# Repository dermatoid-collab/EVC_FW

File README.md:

# EVC_FW

Progetto hardware e firmware del sistema di controllo di un ascensore domestico a trazione (TTF) di LiftingItalia s.r.l. Quattro schede basate su STM32F446, collegate in CAN; il motore è comandato da un VFD.

## Struttura

| Cartella | Contenuto |
|---|---|
| `TTF-Base/` | Scheda master (STM32F446VC, PCB a 4 strati): schemi e PCB KiCad, Gerber/PDF in `fabs/`, firmware in `Firmware/TTF-Base/`. |
| `TTF-CX/` | Scheda di tetto cabina (STM32F446RC, PCB a 4 strati): ingressi di sicurezza S3/S4, bypass trap/tray, zone di sblocco, cella di carico, illuminazione. Firmware in `Firmware/TTF-CX/`. |
| `UDEC.CX/` | Scheda collegata alla cabina (STM32F446VC, PCB a 4 strati): audio, pulsantiera, interfaccia VFD, cella di carico. Firmware in `CubeMX/`, simulazioni in `LTSpice/`. |
| `Schema Macchina/` | Schema elettrico generale dell'impianto (cabina, cappello, servizi); PDF in `fabs/TTF.pdf`. |
| `F510.05.9019 Scheda Consenso Paracadute/` | PCB a 1 strato della scheda di consenso paracadute e modelli FreeCAD del sensore. |

## Firmware TTF-Base

Super-loop con timer software e macchina a stati, in C (STM32CubeIDE/HAL). Moduli principali in `TTF-Base/Firmware/TTF-Base/Core/`:

- `run_mode.c`: macchina a stati del movimento (`NORMAL`, `UP`, `DOWN`, `OPEN_DOOR`, `CLOSE_DOOR`, `STUCK_UP`, `FALL_TEST`, `WAIT_FOR_CALL_RELEASE`) e sequenza di abilitazione.
- `door.c`: ciclo porte (apertura, chiusura, blocco, sblocco).
- `pmode.c`, `battery.c`, `npb.c`, `ltc2959.c`: commutazione caricabatteria/VFD, gestione e misura della batteria.
- `vfd.c`: comando dell'azionamento (CANopen).
- `trips.c`, `trip_list.h`: gestione degli errori (inattivo, attivo, memorizzato).
- `udec_c.c`, `udec_cx.c`, `l2d.c`, `can.c`: comunicazione CAN con le altre schede.
- `HMI.c`, `HMI_menu.c`, `lcd_hd44780_i2c.c`: display LCD e menu.

Le modifiche recenti sono descritte in `TTF-Base/Firmware/TTF-Base/Changelog`.

## Documentazione

- **`docs/registro_issue.md`: documento base del lavoro.** Tutte le osservazioni, le proposte di correzione, le verifiche e il loro stato. Si aggiorna a ogni issue risolta; il controllo di coerenza è `python3 docs/check_registro.py`.
- `docs/analisi.md`: analisi di partenza (panoramica, revisione del codice di sicurezza, catena delle sicurezze, confronto con i manuali).
- I diagrammi stanno in `docs/diagrammi/`, numerati 01-07; gli script che li generano restano in `docs/`.
- `docs/diagrammi/02.diagramma_funzionale.svg` (e `.png`): diagramma funzionale della macchina (stati del movimento, ciclo porta, alimentazione, batteria, sicurezze, comunicazioni), con i riquadri rossi che rimandano agli ID del registro. Si rigenera con `python3 docs/gen_diagramma_funzionale.py docs/diagrammi/02.diagramma_funzionale.svg`.
- `docs/diagrammi/03.diagramma_funzionale_light.svg` (e `.png`): versione del diagramma funzionale per il dipartimento commerciale (blocchi, una corsa passo per passo, stati, sicurezze, dati di prodotto). Si rigenera con `python3 docs/gen_diagramma_light.py docs/diagrammi/03.diagramma_funzionale_light.svg`.
- `docs/diagrammi/04.diagramma_energia_light.svg` (e `.png`): diagramma per il commerciale su ciclo della batteria, contrappesi, autonomia e costi (numeri di esempio con ipotesi dichiarate). Si rigenera con `python3 docs/gen_diagramma_energia.py docs/diagrammi/04.diagramma_energia_light.svg`.
- `docs/diagrammi/05.diagramma_energia_sintesi.svg` (e `.png`): versione sintetica e visuale del diagramma energia, in valutazione. Si rigenera con `python3 docs/gen_diagramma_energia_sintesi.py docs/diagrammi/05.diagramma_energia_sintesi.svg`.
- `docs/diagrammi/07.diagramma_manutenzione_sintesi.svg` (e `.png`): versione sintetica della scheda sulla manutenzione, con il costo delle parti di consumo come stima del costruttore. Si rigenera con `python3 docs/gen_diagramma_manutenzione_sintesi.py docs/diagrammi/07.diagramma_manutenzione_sintesi.svg`.
- `docs/diagrammi/06.diagramma_manutenzione.svg` (e `.png`): scheda commerciale sulla manutenzione, con le sole affermazioni confermate. Si rigenera con `python3 docs/gen_diagramma_manutenzione.py docs/diagrammi/06.diagramma_manutenzione.svg`.
- `docs/diagrammi/01.schema_funzionale.svg` (e `.png`): schema funzionale elettrico con la catena delle sicurezze. Si rigenera con `python3 docs/gen_schema_funzionale.py docs/diagrammi/01.schema_funzionale.svg`.
- `docs/revisione_ST.TEC.068.md`: revisione completa della relazione di calcolo ST.TEC.068 Rev.0 (verifiche ricalcolate, rilievi, domande al progettista).
- `docs/richiesta_correzione_refusi.md`: richiesta di correzione di residui da altri prodotti e refusi nei manuali (DOC-24).
- `docs/proposta_sincronizzazione.md`: proposta di sincronizzazione TortoiseGit → GitHub per il periodo di test (nulla è attivato).
- `docs/proposte_firmware.md`: riassunto delle proposte FW-33 e FW-34 da sottoporre al tecnico del firmware (nessuna modifica applicata).
- `docs/commerciale.md`: appunti sul posizionamento commerciale (USP, brevetti e modelli), da elaborare.
- `CLAUDE.md`: regole di lavoro per questo repository.

## Strumenti

- Schemi e PCB: KiCad.
- Firmware: STM32CubeIDE, progetti configurati con file `.ioc` (CubeMX).
- Simulazioni: LTspice (`UDEC.CX/LTSpice/`).
- Modelli meccanici: FreeCAD.

## Note

- `Drivers/` e `Middlewares/` (HAL e USB di ST) sono inclusi nel repo, così il firmware compila senza rigenerare il codice.
- Cache, file di lock, backup e output di build sono esclusi dal `.gitignore`.
- Il sistema ha funzioni di sicurezza (paracadute, catena di sicurezze, bypass, extracorsa): ogni modifica va validata secondo le norme di prodotto.

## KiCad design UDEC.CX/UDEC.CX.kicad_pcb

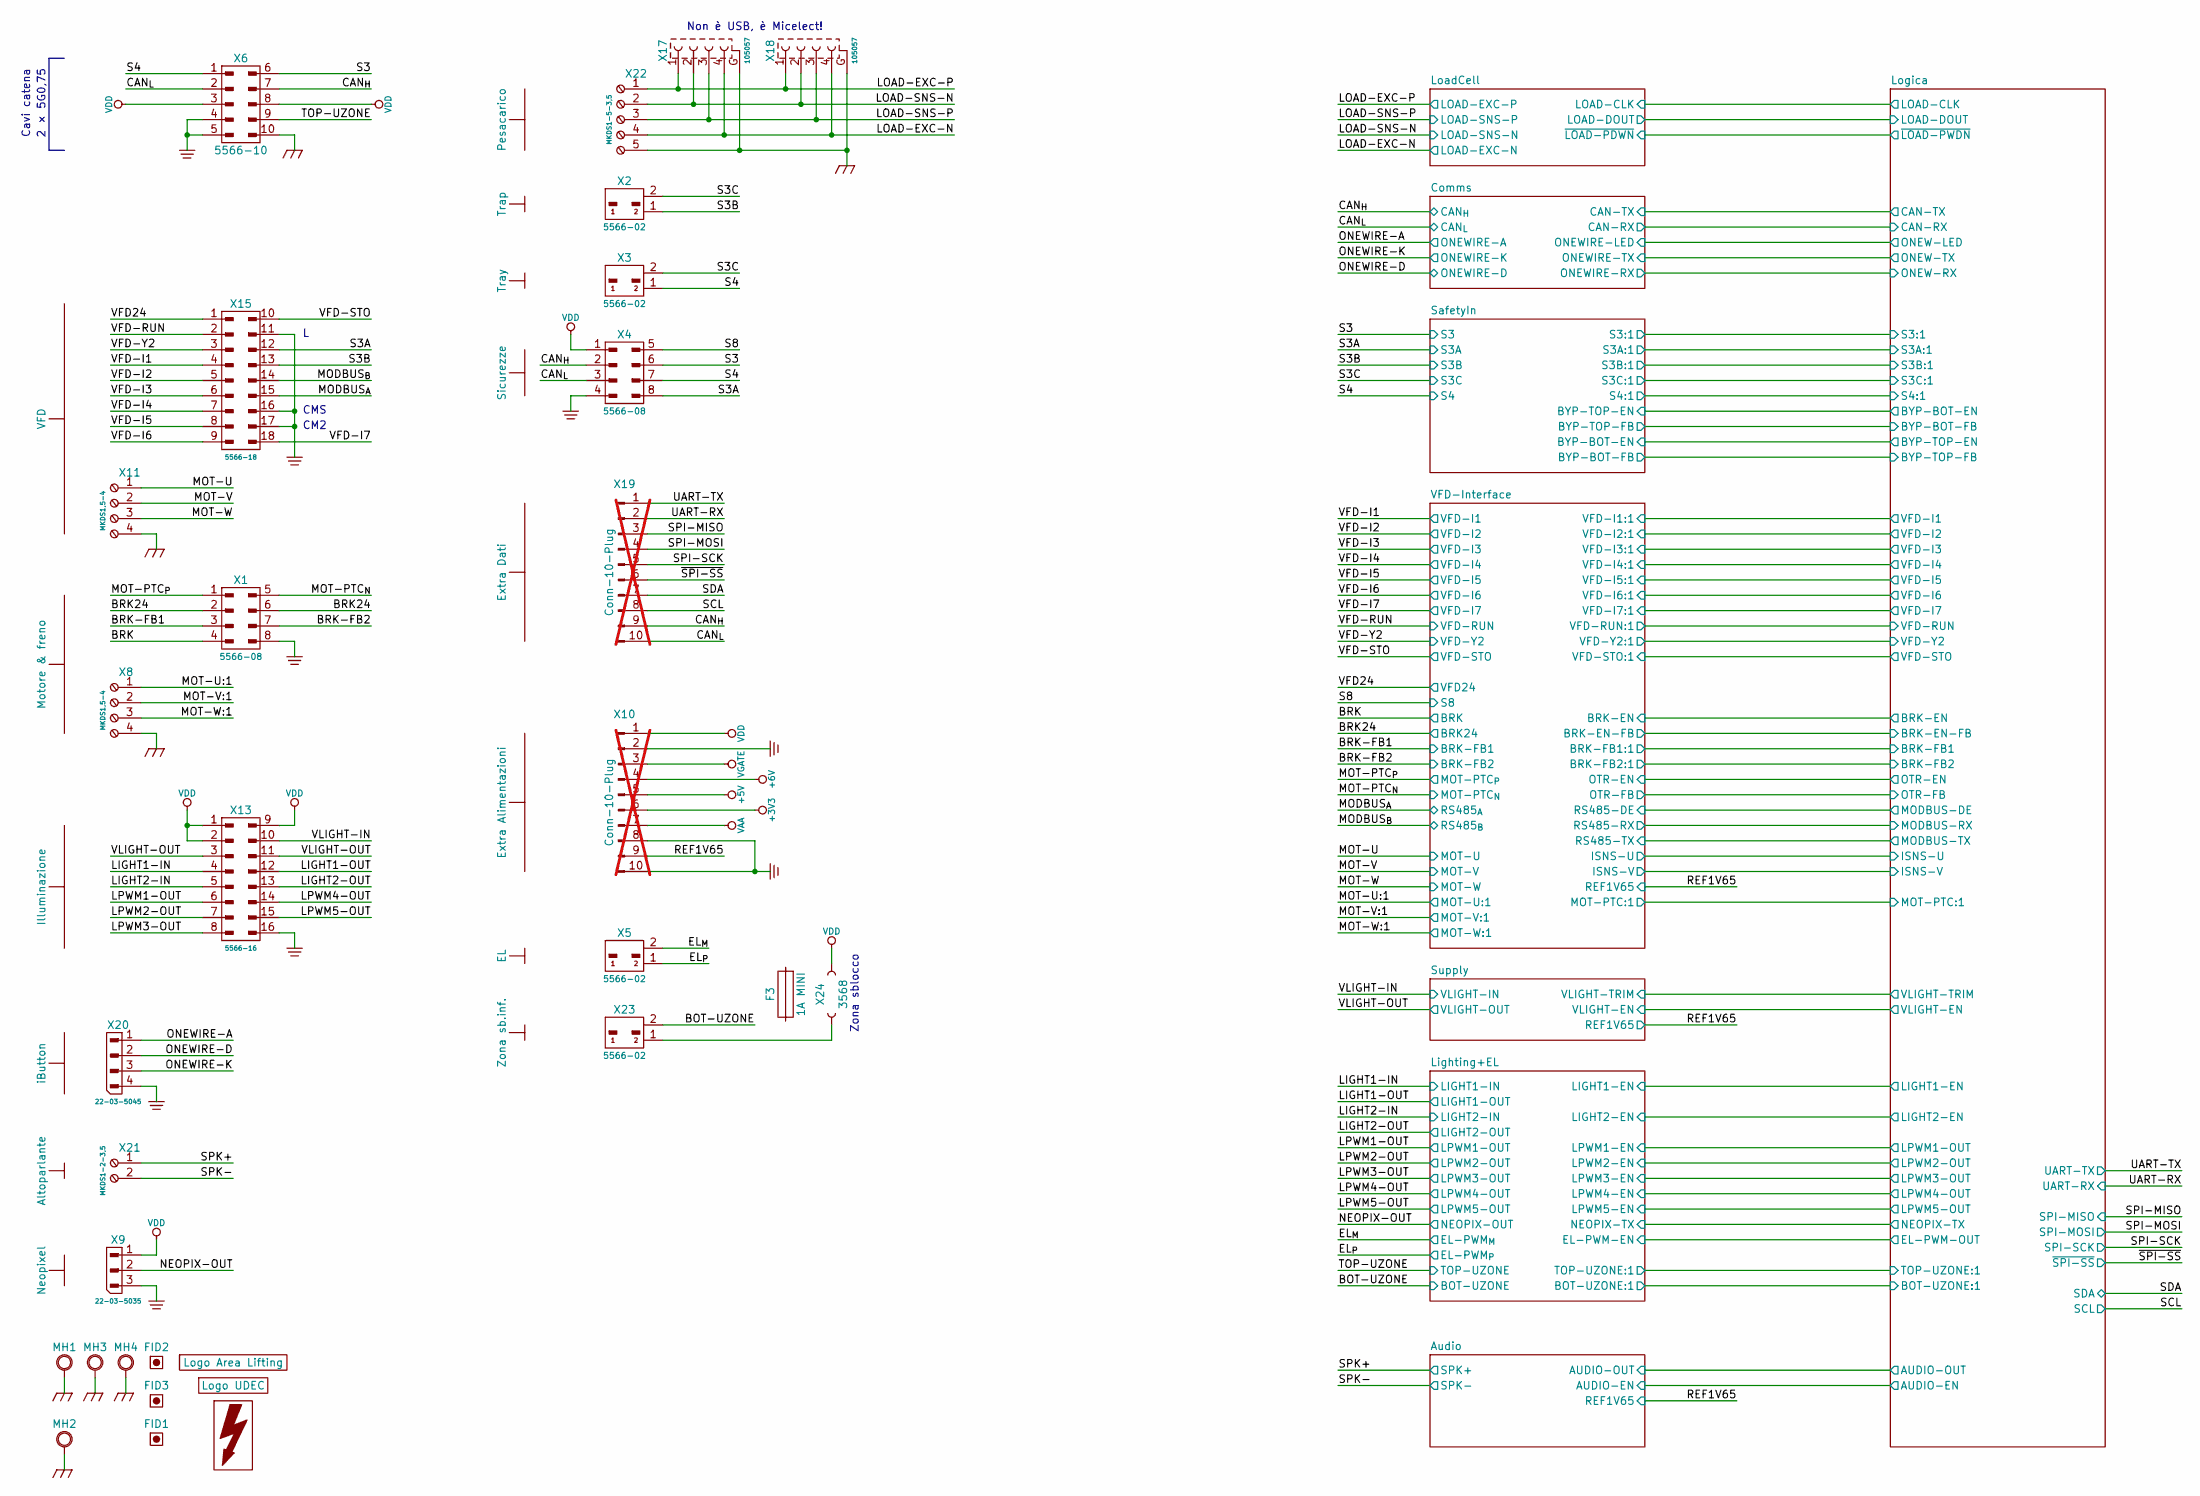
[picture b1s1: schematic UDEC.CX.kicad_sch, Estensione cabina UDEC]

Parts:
F3: 1A MINI; MINI-Fuse
FID1, FID2, FID3: Fiducial; Fid-10
MH1, MH2, MH3, MH4: Hole; Hole-M4
X1, X4: 5566-08
X2, X3, X5, X23: 5566-02
X6: 5566-10
X8, X11: MKDS1,5-4
X9: 22-03-5035
X10, X19: Conn-10-Plug; M-10; not fitted
X13: 5566-16
X15: 5566-18
X17, X18: 105057; Molex-105057
X20: 22-03-5045
X21: MKDS1-2-3,5
X22: MKDS1-5-3,5
X24: 3568; Keystone-3568
ZZZ2: VFD
ZZZ3: Motore & freno
ZZZ4: Illuminazione
ZZZ5: iButton
ZZZ6: Altoparlante
ZZZ7: Neopixel
ZZZ8: Pesacarico
ZZZ9: Trap
ZZZ10: Tray
ZZZ11: Sicurezze
ZZZ12: Extra Dati
ZZZ13: Extra Alimentazioni
ZZZ16: Logo-AreaLifting
ZZZ17: Logo-UDEC; Logo-UDEC-Silk
ZZZ18: Flash-Large
ZZZ19: EL
ZZZ20: Zona sb.inf.

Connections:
+3V3: X10.6; also elsewhere on the board
+5V: X10.5; also elsewhere on the board
+6V: X10.4; also elsewhere on the board
/BOT-UZONE: X23.2; also elsewhere on the board
/BRK: X1.4; also elsewhere on the board
/BRK24: X1.2, X1.6; also elsewhere on the board
/BRK-FB1: X1.3; also elsewhere on the board
/BRK-FB2: X1.7; also elsewhere on the board
/CAN_{H}: X4.2, X6.7, X19.9 (7); also elsewhere on the board
/CAN_{L}: X4.3, X6.2, X19.10 (8); also elsewhere on the board
/EL_{M}: X5.2; also elsewhere on the board
/EL_{P}: X5.1; also elsewhere on the board
/LIGHT1-IN: X13.4; also elsewhere on the board
/LIGHT1-OUT: X13.12; also elsewhere on the board
/LIGHT2-IN: X13.5; also elsewhere on the board
/LIGHT2-OUT: X13.13; also elsewhere on the board
/LOAD-EXC-N: X17.4 (GND), X18.4 (GND), X22.4; also elsewhere on the board
/LOAD-EXC-P: X17.1 (VBUS), X18.1 (VBUS), X22.1; also elsewhere on the board
/LOAD-SNS-N: X17.2 (D-), X18.2 (D-), X22.2; also elsewhere on the board
/LOAD-SNS-P: X17.3 (D+), X18.3 (D+), X22.3; also elsewhere on the board
/LPWM1-OUT: X13.6; also elsewhere on the board
/LPWM2-OUT: X13.7; also elsewhere on the board
/LPWM3-OUT: X13.8; also elsewhere on the board
/LPWM4-OUT: X13.14; also elsewhere on the board
/LPWM5-OUT: X13.15; also elsewhere on the board
/MODBUS_{A}: X15.15; also elsewhere on the board
/MODBUS_{B}: X15.14; also elsewhere on the board
/MOT-PTC_{N}: X1.5; also elsewhere on the board
/MOT-PTC_{P}: X1.1; also elsewhere on the board
/MOT-U: X11.1; also elsewhere on the board
/MOT-U:1: X8.1; also elsewhere on the board
/MOT-V: X11.2; also elsewhere on the board
/MOT-V:1: X8.2; also elsewhere on the board
/MOT-W: X11.3; also elsewhere on the board
/MOT-W:1: X8.3; also elsewhere on the board
/NEOPIX-OUT: X9.2; also elsewhere on the board
/ONEWIRE-A: X20.1; also elsewhere on the board
/ONEWIRE-D: X20.2; also elsewhere on the board
/ONEWIRE-K: X20.3; also elsewhere on the board
/REF1V65: X10.9 (7); also elsewhere on the board
/S3: X4.6, X6.6; also elsewhere on the board
/S3A: X4.8, X15.12; also elsewhere on the board
/S3B: X2.1, X15.13; also elsewhere on the board
/S3C: X2.2, X3.2; also elsewhere on the board
/S4: X3.1, X4.7, X6.1; also elsewhere on the board
/S8: X4.5; also elsewhere on the board
/SCL: X19.8; also elsewhere on the board
/SDA: X19.7; also elsewhere on the board
/SPI-MISO: X19.3; also elsewhere on the board
/SPI-MOSI: X19.4; also elsewhere on the board
/SPI-SCK: X19.5; also elsewhere on the board
/SPK+: X21.1; also elsewhere on the board
/SPK-: X21.2; also elsewhere on the board
/TOP-UZONE: X6.9; also elsewhere on the board
/UART-RX: X19.2; also elsewhere on the board
/UART-TX: X19.1; also elsewhere on the board
/VFD24: X15.1; also elsewhere on the board
/VFD-I1: X15.4; also elsewhere on the board
/VFD-I2: X15.5; also elsewhere on the board
/VFD-I3: X15.6; also elsewhere on the board
/VFD-I4: X15.7; also elsewhere on the board
/VFD-I5: X15.8; also elsewhere on the board
/VFD-I6: X15.9; also elsewhere on the board
/VFD-I7: X15.18; also elsewhere on the board
/VFD-RUN: X15.2; also elsewhere on the board
/VFD-STO: X15.10; also elsewhere on the board
/VFD-Y2: X15.3; also elsewhere on the board
/VLIGHT-IN: X13.10; also elsewhere on the board
/VLIGHT-OUT: X13.3, X13.11; also elsewhere on the board
/~SPI-SS: X19.6; also elsewhere on the board
CHASSIS: MH1.HOLE (HOLE_HOLE), MH2.HOLE (HOLE_HOLE), MH3.HOLE (HOLE_HOLE), MH4.HOLE (HOLE_HOLE), X6.10, X8.4, X11.4, X17.G, X18.G, X22.5 (P4)
GND: X1.8, X4.4, X6.4, X6.5, X9.3, X10.2, X10.8, X10.10 (8), X13.16, X15.11, X15.16, X15.17, X20.4; also elsewhere on the board
unnamed: X23.1, X24.1
VAA: X10.7; also elsewhere on the board
VDD: X4.1, X6.3, X6.8, X9.1, X10.1, X13.1, X13.2, X13.9, X24.2; also elsewhere on the board
VGATE: X10.3; also elsewhere on the board

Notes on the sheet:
Zona sblocco
2 × 5G0,75
CM2
Cavi catena
Non è USB, è Micelect!
CMS

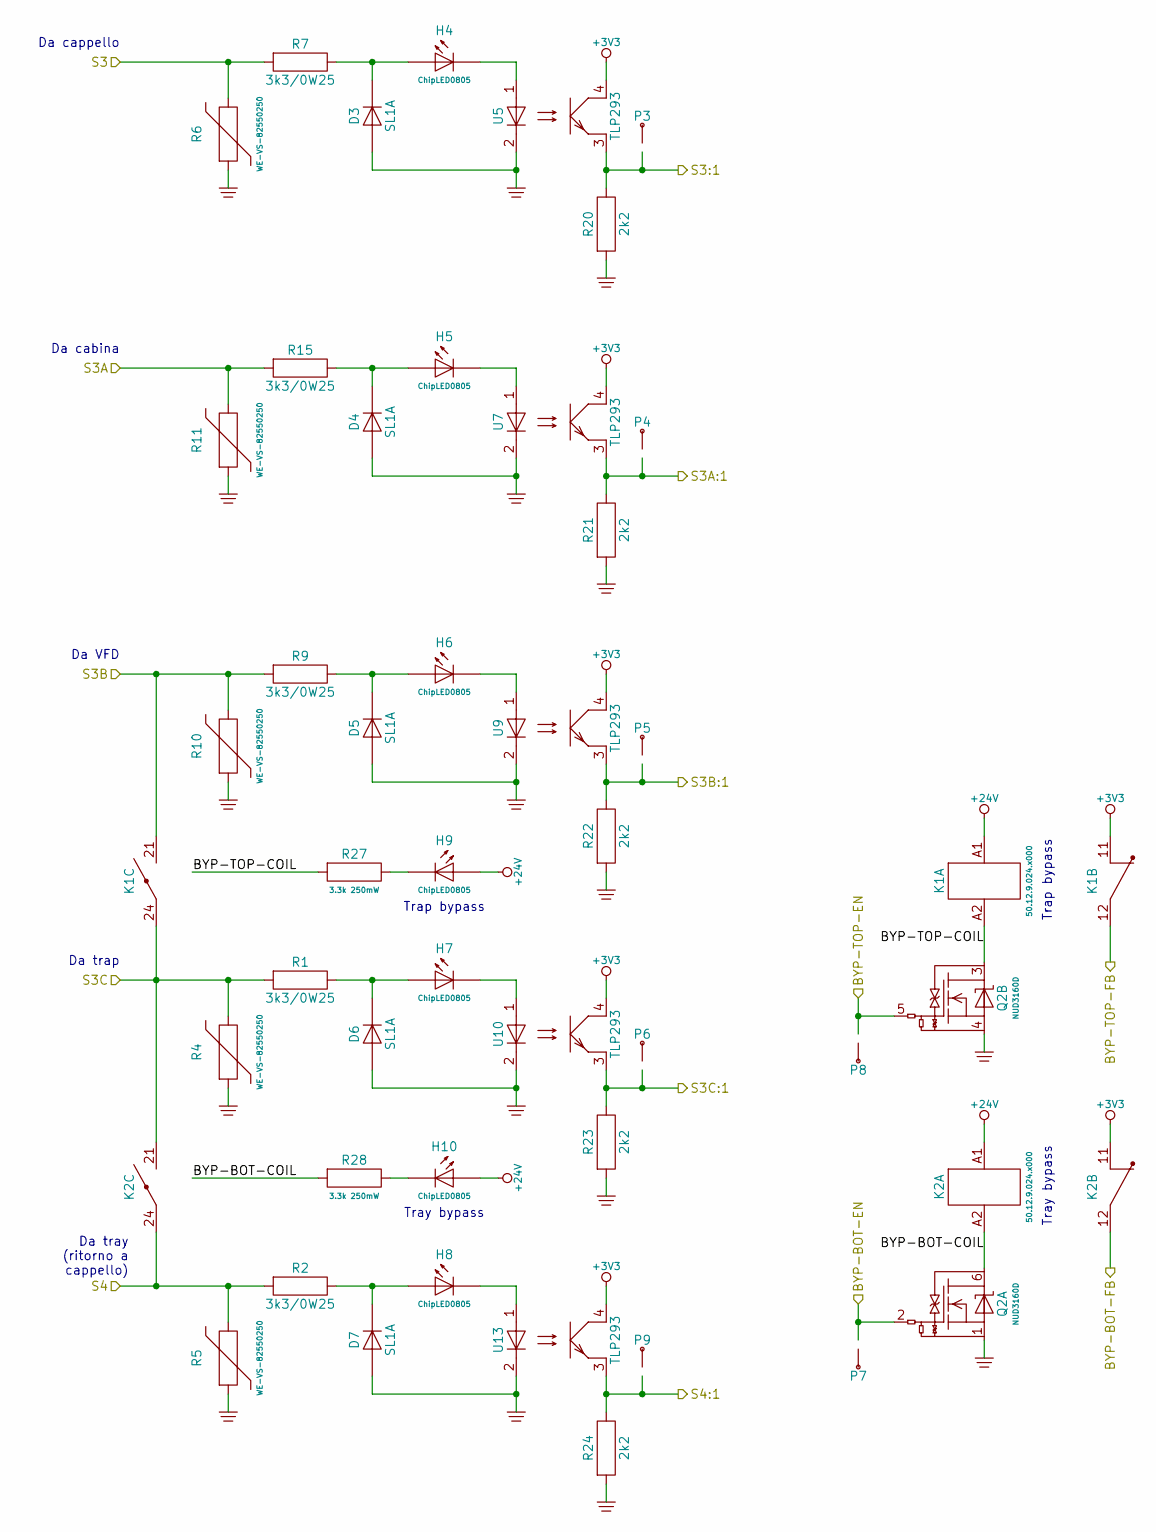
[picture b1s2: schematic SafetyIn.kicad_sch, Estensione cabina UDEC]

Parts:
D3, D4, D5, D6, D7: SL1A; SOD123FL
H4, H5, H6, H7, H8, H9, H10: ChipLED0805; Chipled-0805
K1, K2: 50.12.9.024.x000; 50.12
P3, P4, P5, P6, P7, P8, P9: PinTst
Q2: NUD3160D; MO193AA
R1, R2, R7, R9, R15: 3k3/0W25; R1206
R4, R5, R6, R10, R11: WE-VS-82550250; WE-VS-0805
R20, R21, R22, R23, R24: 2k2; R0603
R27, R28: 3.3k 250mW; R1206
U5, U7, U9, U10, U13: TLP293; Toshiba-11-3C1

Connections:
+3V3: K1.11, K2.11, U5.4 (C), U7.4 (C), U9.4 (C), U10.4 (C), U13.4 (C); also elsewhere on the board
+24V: H9.A, H10.A, K1.A1, K2.A1; also elsewhere on the board
/Logica/BYP-BOT-EN: P8.1, Q2.5 (G); also elsewhere on the board
/Logica/BYP-BOT-FB: K1.12; also elsewhere on the board
/Logica/BYP-TOP-EN: P7.1, Q2.2 (G); also elsewhere on the board
/Logica/BYP-TOP-FB: K2.12; also elsewhere on the board
/Logica/S3:1: P3.1, R20.1, U5.3 (E); also elsewhere on the board
/Logica/S3A:1: P4.1, R21.1, U7.3 (E); also elsewhere on the board
/Logica/S3B:1: P5.1, R22.1, U9.3 (E); also elsewhere on the board
/Logica/S3C:1: P6.1, R23.1, U10.3 (E); also elsewhere on the board
/Logica/S4:1: P9.1, R24.1, U13.3 (E); also elsewhere on the board
/S3: R6.2, R7.2; also elsewhere on the board
/S3A: R11.2, R15.2; also elsewhere on the board
/S3B: K1.21, R9.2, R10.2; also elsewhere on the board
/S3C: K1.24, K2.21, R1.2, R4.2; also elsewhere on the board
/S4: K2.24, R2.2, R5.2; also elsewhere on the board
/SafetyIn/BYP-BOT-COIL: K2.A2, Q2.6 (D), R28.2
/SafetyIn/BYP-TOP-COIL: K1.A2, Q2.3 (D), R27.2
GND: D3.A, D4.A, D5.A, D6.A, D7.A, Q2.1 (4), Q2.4, R4.1, R5.1, R6.1, R10.1, R11.1, R20.2, R21.2, R22.2, R23.2, R24.2, U5.2 (K), U7.2 (K), U9.2 (K), U10.2 (K), U13.2 (K); also elsewhere on the board
unnamed: D3.K, H4.A, R7.1
unnamed: D4.K, H5.A, R15.1
unnamed: D5.K, H6.A, R9.1
unnamed: D6.K, H7.A, R1.1
unnamed: D7.K, H8.A, R2.1
unnamed: H9.K, R27.1
unnamed: H10.K, R28.1
unnamed: H4.K, U5.1 (A)
unnamed: H5.K, U7.1 (A)
unnamed: H6.K, U9.1 (A)
unnamed: H7.K, U10.1 (A)
unnamed: H8.K, U13.1 (A)

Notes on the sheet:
Da cappello
Trap bypass
Da tray (ritorno a cappello)
Tray bypass
Da trap
Da VFD
Da cabina

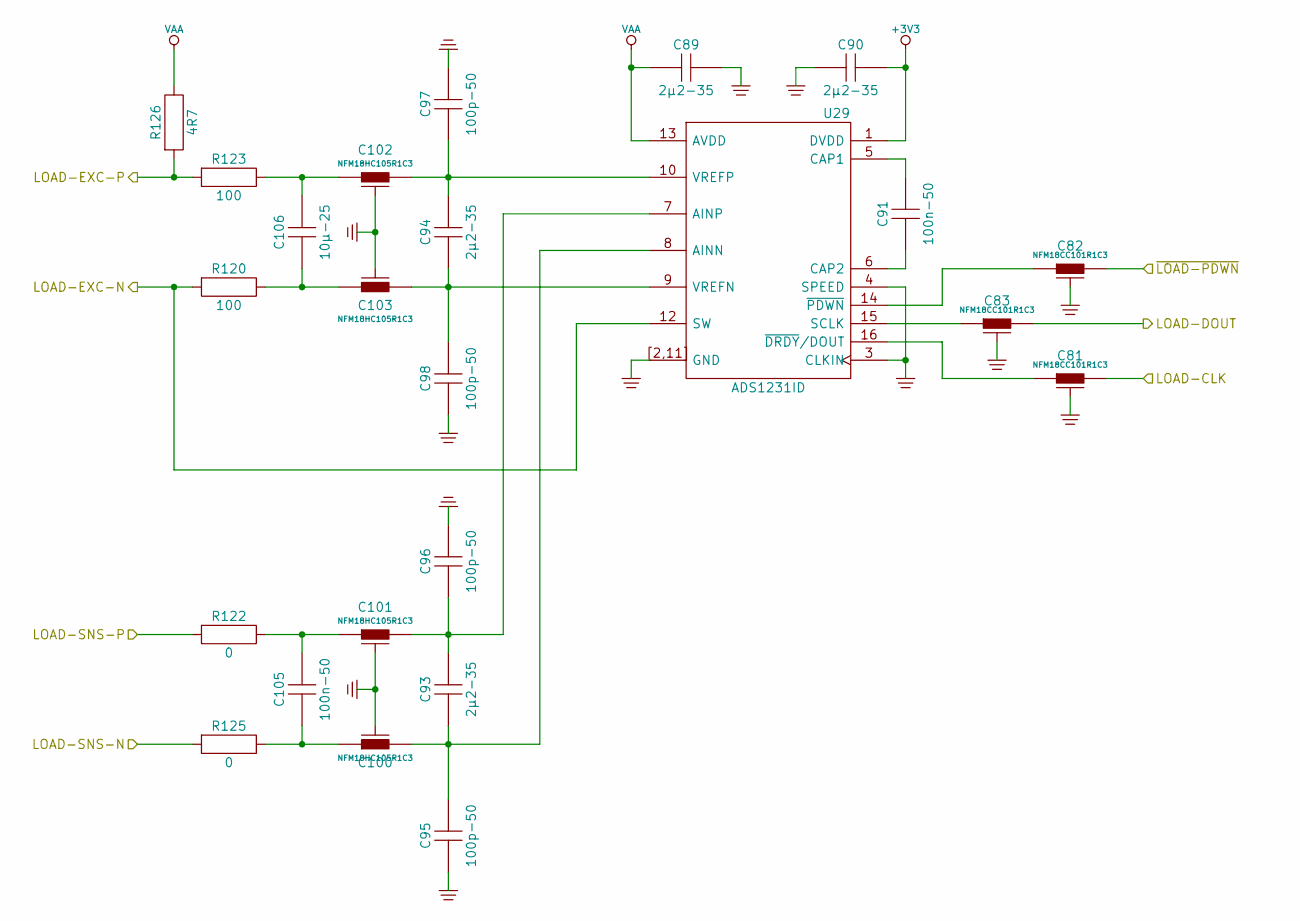
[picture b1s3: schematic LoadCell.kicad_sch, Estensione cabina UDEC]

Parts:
C81, C82, C83: NFM18CC101R1C3; Murata-NFM18CC
C89, C90, C93, C94: 2µ2-35; C0603
C91, C105: 100n-50; C0603
C95, C96, C97, C98: 100p-50; C0603
C100, C101, C102, C103: NFM18HC105R1C3; Murata-NFM18HC105
C106: 10µ-25; C0805
R120, R123: 100; R0603
R122, R125: 0; R0603
R126: 4R7; R0603
U29: ADS1231ID; MS012AC

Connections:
+3V3: C90.2, U29.1 (DVDD); also elsewhere on the board
/LOAD-EXC-N: R120.2, U29.12 (SW); also elsewhere on the board
/LOAD-EXC-P: R123.2, R126.2; also elsewhere on the board
/LOAD-SNS-N: R125.2; also elsewhere on the board
/LOAD-SNS-P: R122.2; also elsewhere on the board
/LoadCell/LOAD-CLK: C81.2; also elsewhere on the board
/LoadCell/LOAD-DOUT: C83.2; also elsewhere on the board
/LoadCell/~LOAD-PDWN: C82.2; also elsewhere on the board
GND: C81.3, C82.3, C83.3, C89.2, C90.1, C95.1, C96.2, C97.2, C98.1, C100.3, C101.3, C102.3, C103.3, U29.2 (GND), U29.3 (CLKIN), U29.4 (SPEED), U29.11 (GND), U29.[2,11] (GND); also elsewhere on the board
unnamed: C100.1, C105.1, R125.1
unnamed: C101.1, C105.2, R122.1
unnamed: C102.1, C106.2, R123.1
unnamed: C103.1, C106.1, R120.1
unnamed: C93.1, C95.2, C100.2, U29.8 (AINN)
unnamed: C93.2, C96.1, C101.2, U29.7 (AINP)
unnamed: C91.2, U29.5 (CAP1)
unnamed: C91.1, U29.6 (CAP2)
unnamed: C83.1, U29.15 (SCLK)
unnamed: C94.1, C98.2, C103.2, U29.9 (VREFN)
unnamed: C94.2, C97.1, C102.2, U29.10 (VREFP)
unnamed: C81.1, U29.16 (~DRDY/DOUT)
unnamed: C82.1, U29.14 (~PDWN)
VAA: C89.1, R126.1, U29.13 (AVDD); also elsewhere on the board

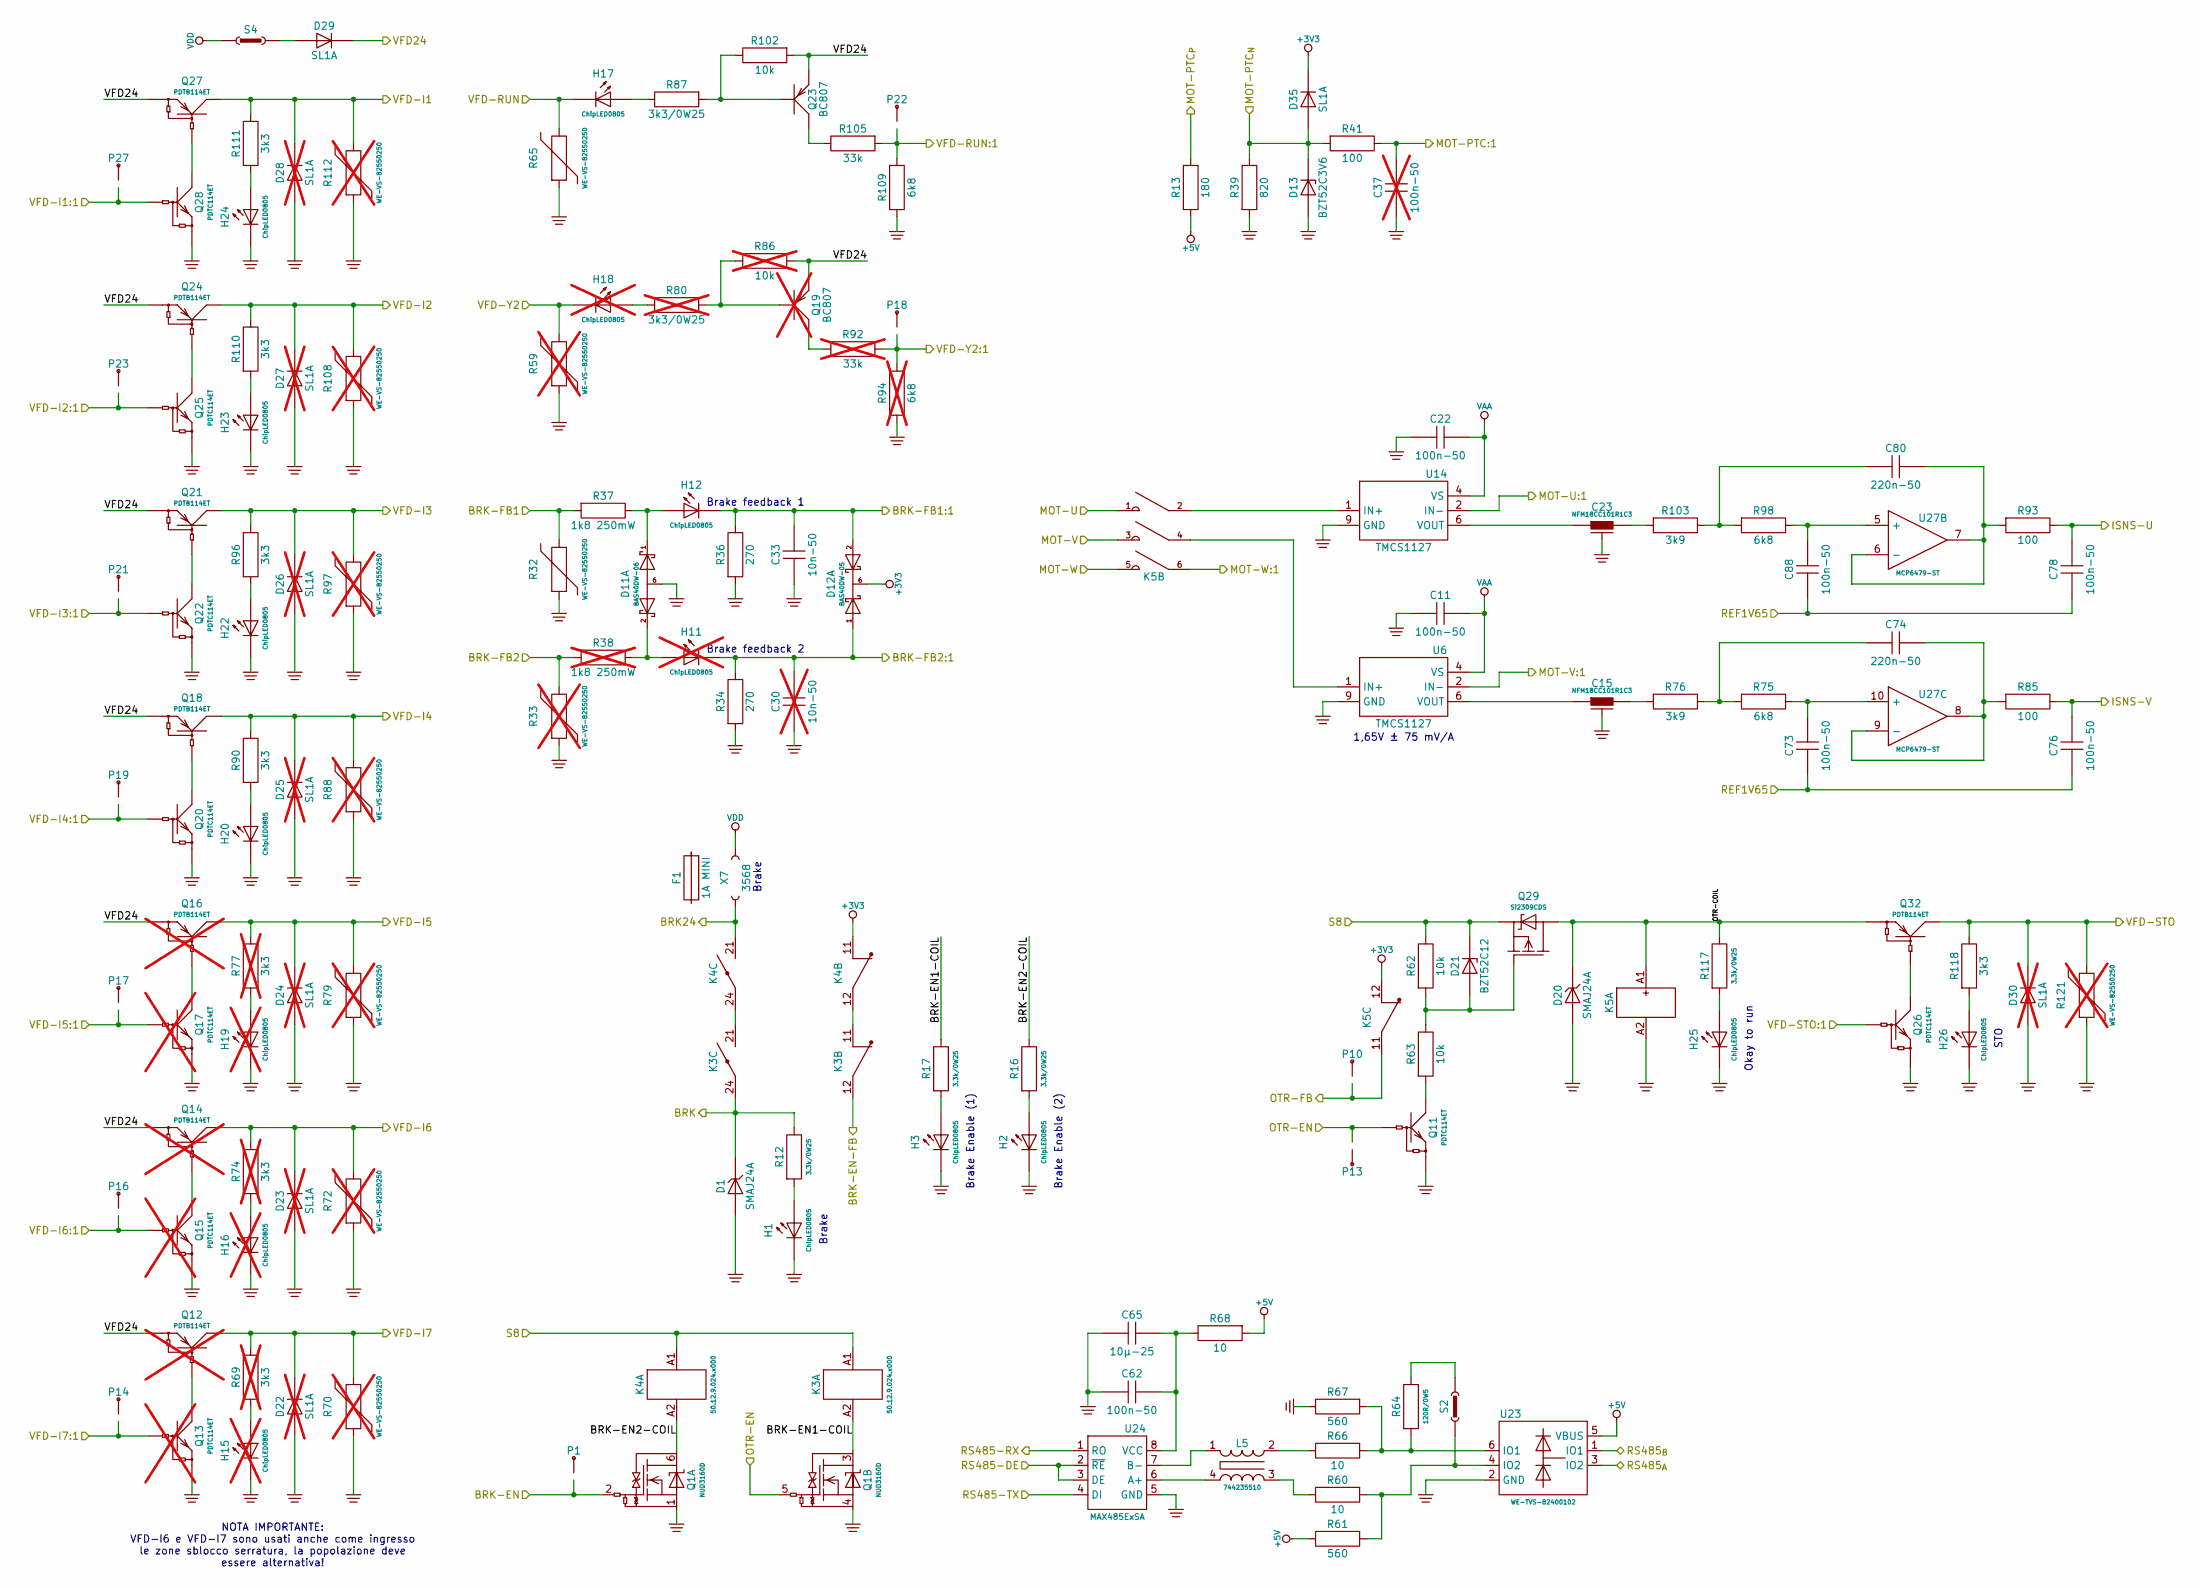
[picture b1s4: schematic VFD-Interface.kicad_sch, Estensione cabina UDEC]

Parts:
C11, C22, C62, C73, C76, C78, C88: 100n-50; C0603
C15, C23: NFM18CC101R1C3; Murata-NFM18CC
C30: 10n-50; C0603; not fitted
C33: 10n-50; C0603
C37: 100n-50; C0603; not fitted
C65: 10µ-25; C0805
C74, C80: 220n-50; C0603
D1, D20: SMAJ24A; DO214AC
D11: BAS40DW-06; MO203AB
D12: BAS40DW-05; MO203AB
D13: BZT52C3V6; SOD123
D21: BZT52C12; SOD123
D22, D23, D24, D25, D26, D27, D28, D30: SL1A; SOD123FL; not fitted
D29, D35: SL1A; SOD123FL
F1: 1A MINI; MINI-Fuse
H1, H2, H3, H12, H17, H20, H22, H23, H24, H25, H26: ChipLED0805; Chipled-0805
H11, H15, H16, H18, H19: ChipLED0805; Chipled-0805; not fitted
K3, K4: 50.12.9.024.x000; 50.12
K5: 11BGP0901D024; Lovato-11BGP0901D024
L5: 744235510; WE-CNSW-1812
P1, P10, P13, P14, P16, P17, P18, P19, P21, P22, P23, P27: PinTst
Q1: NUD3160D; MO193AA
Q11, Q20, Q22, Q25, Q26, Q28: PDTC114ET; TO236-BEC
Q12, Q14, Q16: PDTB114ET; TO236-BEC; not fitted
Q13, Q15, Q17: PDTC114ET; TO236-BEC; not fitted
Q18, Q21, Q24, Q27, Q32: PDTB114ET; TO236-BEC
Q19: BC807; TO236-BEC; not fitted
Q23: BC807; TO236-BEC
Q29: Si2309CDS; TO236-GSD
R12, R16, R17, R117: 3.3k/0W25; R1206
R13: 180; R0603
R32, R65: WE-VS-82550250; WE-VS-0805
R33, R59, R70, R72, R79, R88, R97, R108, R112, R121: WE-VS-82550250; WE-VS-0805; not fitted
R34, R36: 270; R0603
R37: 1k8 250mW; R1206
R38: 1k8 250mW; R1206; not fitted
R39: 820; R0603
R41, R85, R93: 100; R0603
R60, R66, R68: 10; R0603
R61, R67: 560; R0603
R62, R63, R102: 10k; R0603
R64: 120R/0W5; R1210
R69, R74, R77: 3k3; R1206; not fitted
R75, R98, R109: 6k8; R0603
R76, R103: 3k9; R0603
R80: 3k3/0W25; R1206; not fitted
R86: 10k; R0603; not fitted
R87: 3k3/0W25; R1206
R90, R96, R110, R111, R118: 3k3; R1206
R92: 33k; R0603; not fitted
R94: 6k8; R0603; not fitted
R105: 33k; R0603
S2, S4: Jumper-2.54
U6, U14: TMCS1127; TI-DVG10
U23: WE-TVS-82400102; MO178AB
U24: MAX485ExSA; MS012AA
U27: MCP6479-ST; MO153AB1
X7: 3568; Keystone-3568

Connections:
+3V3: D12.6 (K), D35.K, K4.11, K5.12; also elsewhere on the board
+5V: R13.2, R61.1, R68.2, U23.5 (VBUS); also elsewhere on the board
/BRK: D1.K, K3.24, R12.1; also elsewhere on the board
/BRK24: K4.21, X7.1; also elsewhere on the board
/BRK-FB1: R32.2, R37.2; also elsewhere on the board
/BRK-FB2: R33.2, R38.2; also elsewhere on the board
/Logica/BRK-EN: P1.1, Q1.2 (G); also elsewhere on the board
/Logica/BRK-EN-FB: K3.12; also elsewhere on the board
/Logica/BRK-FB1: C33.2, D12.2 (A2), H12.K, R36.1; also elsewhere on the board
/Logica/BRK-FB2: C30.2, D12.1 (A1), H11.K, R34.1; also elsewhere on the board
/Logica/ISNS-U: C78.2, R93.1; also elsewhere on the board
/Logica/ISNS-V: C76.2, R85.1; also elsewhere on the board
/Logica/MODBUS-DE: U24.2 (~RE), U24.3 (DE); also elsewhere on the board
/Logica/MODBUS-RX: U24.1 (RO); also elsewhere on the board
/Logica/MODBUS-TX: U24.4 (DI); also elsewhere on the board
/Logica/MOT-PTC:1: C37.2, R41.1; also elsewhere on the board
/Logica/OTR-EN: P13.1, Q1.5 (G), Q11.B; also elsewhere on the board
/Logica/OTR-FB: K5.11, P10.1; also elsewhere on the board
/Logica/VFD-I1: P27.1, Q28.B; also elsewhere on the board
/Logica/VFD-I2: P23.1, Q25.B; also elsewhere on the board
/Logica/VFD-I3: P21.1, Q22.B; also elsewhere on the board
/Logica/VFD-I4: P19.1, Q20.B; also elsewhere on the board
/Logica/VFD-I5: P17.1, Q17.B; also elsewhere on the board
/Logica/VFD-I6: P16.1, Q15.B; also elsewhere on the board
/Logica/VFD-I7: P14.1, Q13.B; also elsewhere on the board
/Logica/VFD-RUN: P22.1, R105.2, R109.1; also elsewhere on the board
/Logica/VFD-STO: Q26.B; also elsewhere on the board
/Logica/VFD-Y2: P18.1, R92.2, R94.1; also elsewhere on the board
/MODBUS_{A}: U23.3 (IO2); also elsewhere on the board
/MODBUS_{B}: U23.1 (IO1); also elsewhere on the board
/MOT-PTC_{N}: D13.K, D35.A, R39.1, R41.2; also elsewhere on the board
/MOT-PTC_{P}: R13.1; also elsewhere on the board
/MOT-U: K5.1; also elsewhere on the board
/MOT-U:1: U14.2 (IN-); also elsewhere on the board
/MOT-V: K5.3; also elsewhere on the board
/MOT-V:1: U6.2 (IN-); also elsewhere on the board
/MOT-W: K5.5; also elsewhere on the board
/MOT-W:1: K5.6; also elsewhere on the board
/REF1V65: C73.1, C76.1, C78.1, C88.1; also elsewhere on the board
/S8: D21.K, K3.A1, K4.A1, Q29.S, R62.1; also elsewhere on the board
/VFD24: D29.K, Q12.E, Q14.E, Q16.E, Q18.E, Q19.E, Q21.E, Q23.E, Q24.E, Q27.E, R86.2, R102.2; also elsewhere on the board
/VFD-I1: D28.K, Q27.C, R111.1, R112.2; also elsewhere on the board
/VFD-I2: D27.K, Q24.C, R108.2, R110.1; also elsewhere on the board
/VFD-I3: D26.K, Q21.C, R96.1, R97.2; also elsewhere on the board
/VFD-I4: D25.K, Q18.C, R88.2, R90.1; also elsewhere on the board
/VFD-I5: D24.K, Q16.C, R77.1, R79.2; also elsewhere on the board
/VFD-I6: D23.K, Q14.C, R72.2, R74.1; also elsewhere on the board
/VFD-I7: D22.K, Q12.C, R69.1, R70.2; also elsewhere on the board
/VFD-Interface/BRK-EN1-COIL: K3.A2, Q1.3 (D), R17.1
/VFD-Interface/BRK-EN2-COIL: K4.A2, Q1.6 (D), R16.1
/VFD-Interface/OTR-COIL: D20.K, K5.A1, Q29.D, Q32.E, R117.1
/VFD-RUN: H17.K, R65.2; also elsewhere on the board
/VFD-STO: D30.K, Q32.C, R118.1, R121.2; also elsewhere on the board
/VFD-Y2: H18.K, R59.2; also elsewhere on the board
GND: C11.2, C15.3, C22.2, C23.3, C30.1, C33.1, C37.1, C62.2, C65.2, D1.A, D11.6 (A), D13.A, D20.A, D22.A, D23.A, D24.A, D25.A, D26.A, D27.A, D28.A, D30.A, H1.K, H2.K, H3.K, H15.K, H16.K, H19.K, H20.K, H22.K, H23.K, H24.K, H25.K, H26.K, K5.A2, Q1.1 (4), Q1.4, Q11.E, Q13.E, Q15.E, Q17.E, Q20.E, Q22.E, Q25.E, Q26.E, Q28.E, R32.1, R33.1, R34.2, R36.2, R39.2, R59.1, R65.1, R67.1, R70.1, R72.1, R79.1, R88.1, R94.2, R97.1, R108.1, R109.2, R112.1, R121.1, U6.9 (GND), U14.9 (GND), U23.2 (GND), U24.5 (GND); also elsewhere on the board
unnamed: C15.2, R76.2
unnamed: C23.2, R103.2
unnamed: C74.1, R75.2, R76.1
unnamed: C80.1, R98.2, R103.1
unnamed: D11.1 (K1), H12.A, R37.1
unnamed: D11.2 (K2), H11.A, R38.1
unnamed: D21.A, Q29.G, R62.2, R63.1
unnamed: D29.A, S4.2
unnamed: H1.A, R12.2
unnamed: H2.A, R16.2
unnamed: H3.A, R17.2
unnamed: H15.A, R69.2
unnamed: H16.A, R74.2
unnamed: H17.A, R87.1
unnamed: H18.A, R80.1
unnamed: H19.A, R77.2
unnamed: H20.A, R90.2
unnamed: H22.A, R96.2
unnamed: H23.A, R110.2
unnamed: H24.A, R111.2
unnamed: H25.A, R117.2
unnamed: H26.A, R118.2
unnamed: K3.11, K4.12
unnamed: K3.21, K4.24
unnamed: L5.2, R66.1
unnamed: L5.3, R60.1
unnamed: Q11.C, R63.2
unnamed: Q12.B, Q13.C
unnamed: Q14.B, Q15.C
unnamed: Q16.B, Q17.C
unnamed: Q18.B, Q20.C
unnamed: Q19.B, R80.2, R86.1
unnamed: Q19.C, R92.1
unnamed: Q21.B, Q22.C
unnamed: Q23.B, R87.2, R102.1
unnamed: Q23.C, R105.1
unnamed: Q24.B, Q25.C
unnamed: Q26.C, Q32.B
unnamed: Q27.B, Q28.C
unnamed: R60.2, R61.2, S2.2, U23.4 (IO2)
unnamed: R64.1, S2.1
unnamed: R64.2, R66.2, R67.2, U23.6 (IO1)
unnamed: K5.4, U6.1 (IN+)
unnamed: C15.1, U6.6 (VOUT)
unnamed: K5.2, U14.1 (IN+)
unnamed: C23.1, U14.6 (VOUT)
unnamed: L5.4, U24.6 (A+)
unnamed: L5.1, U24.7 (B-)
unnamed: C62.1, C65.1, R68.1, U24.8 (VCC)
unnamed: C88.2, R98.1, U27.5 (+)
unnamed: C80.2, R93.2, U27.6 (-), U27.7
unnamed: C73.2, R75.1, U27.10 (+)
unnamed: C74.2, R85.2, U27.8, U27.9 (-)
VAA: C11.1, C22.1, U6.4 (VS), U14.4 (VS); also elsewhere on the board
VDD: S4.1, X7.2; also elsewhere on the board

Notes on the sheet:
STO
1,65V ± 75 mV/A
Brake Enable (2)
Brake Enable (1)
Brake
Okay to run
Brake feedback 2
Brake feedback 1
NOTA IMPORTANTE: VFD-I6 e VFD-I7 sono usati anche come ingresso le zone sblocco serratura, la popolazione deve essere alternativa!
